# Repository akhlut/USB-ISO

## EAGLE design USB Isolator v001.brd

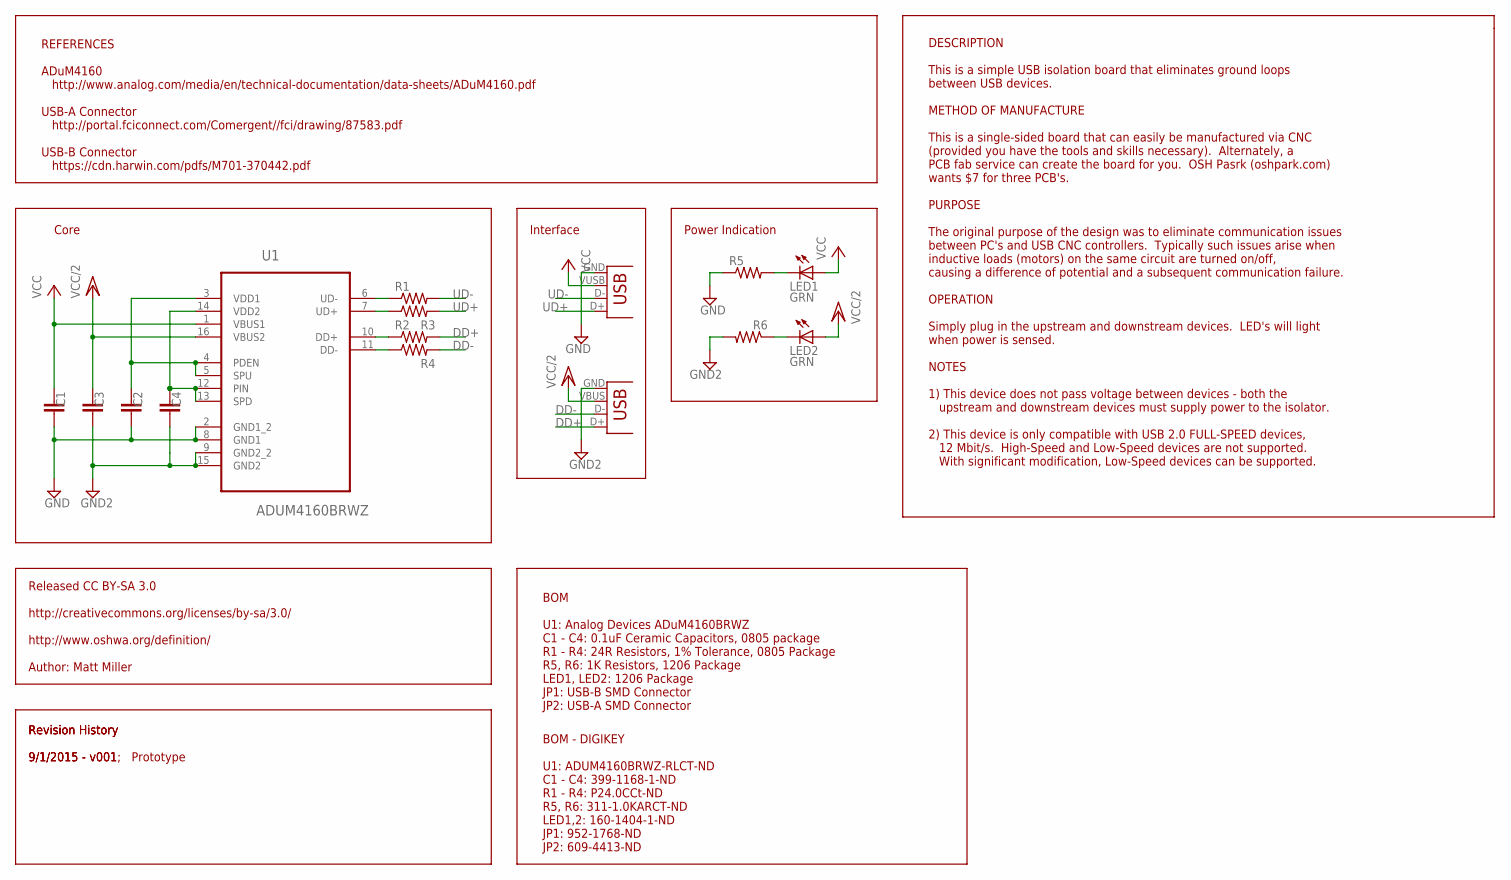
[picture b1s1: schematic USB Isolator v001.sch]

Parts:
C1, C2, C3, C4: 0.1uF; 0805
JP1: USB-B-S; USB-B-SMT
JP2: USB-A-S
LED1, LED2: GRN; LED-1206
R1, R2, R3, R4: 25; 0805
R5, R6: 1K; 1206
U1: ADUM4160BRWZ; SOIC127P1032X265-16N

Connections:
DD+: JP2.D+, R4.2
DD-: JP2.D-, R3.2
GND: C1.2, C2.2, JP1.GND, R5.1, U1.2 (GND1_2), U1.8 (GND1)
GND2: C3.2, C4.2, JP2.GND, R6.2, U1.9 (GND2_2), U1.15 (GND2)
unnamed: LED1.C, R5.2
unnamed: C2.1, U1.3 (VDD1), U1.4 (PDEN), U1.5 (SPU)
unnamed: LED2.C, R6.1
unnamed: C4.1, U1.12 (PIN), U1.13 (SPD), U1.14 (VDD2)
unnamed: R1.1, U1.6 (UD-)
unnamed: R2.1, U1.7 (UD+)
unnamed: R4.1, U1.10 (DD+)
unnamed: R3.1, U1.11 (DD-)
UD+: JP1.D+, R2.2
UD-: JP1.D-, R1.2
VCC: C1.1, JP1.VUSB (VBUS), LED1.A, U1.1 (VBUS1)
VCC/2: C3.1, JP2.VBUS, LED2.A, U1.16 (VBUS2)

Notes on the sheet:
REFERENCES ADuM4160 http://www.analog.com/media/en/technical-documentation/data-sheets/ADuM4160.pdf USB-A Connector http://portal.fciconnect.com/Comergent//fci/drawing/87583.pdf USB-B Connector https://cdn.harwin.com/pdfs/M701-370442.pdf
BOM U1: Analog Devices ADuM4160BRWZ C1 - C4: 0.1uF Ceramic Capacitors, 0805 package R1 - R4: 24R Resistors, 1% Tolerance, 0805 Package R5, R6: 1K Resistors, 1206 Package LED1, LED2: 1206 Package JP1: USB-B SMD Connector JP2: USB-A SMD Connector
Core
Interface
Power Indication
Released CC BY-SA 3.0 http://creativecommons.org/licenses/by-sa/3.0/ http://www.oshwa.org/definition/ Author: Matt Miller
DESCRIPTION This is a simple USB isolation board that eliminates ground loops between USB devices. METHOD OF MANUFACTURE This is a single-sided board that can easily be manufactured via CNC (provided you have the tools and skills necessary). Alternately, a PCB fab service can create the board for y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
Revision History 9/1/2015 - v001; Prototype
Revision History 9/1/2015 - v001
BOM - DIGIKEY U1: ADUM4160BRWZ-RLCT-ND C1 - C4: 399-1168-1-ND R1 - R4: P24.0CCt-ND R5, R6: 311-1.0KARCT-ND LED1,2: 160-1404-1-ND JP1: 952-1768-ND JP2: 609-4413-ND

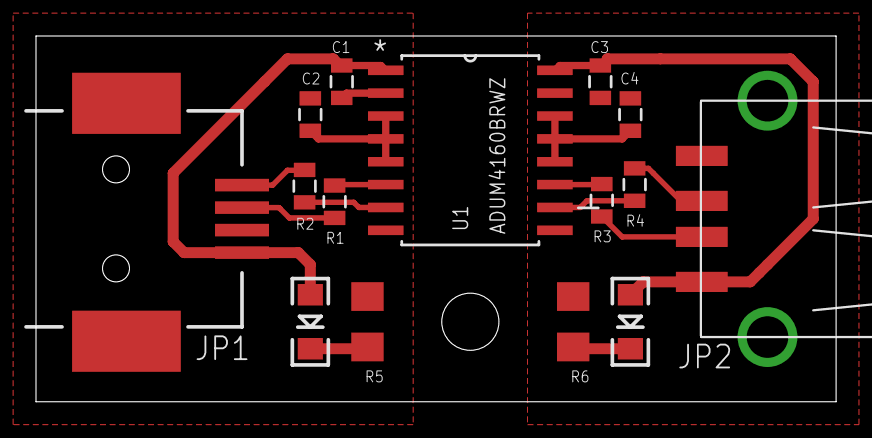
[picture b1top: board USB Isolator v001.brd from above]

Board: 2 copper layers, 44.5 x 20.3 mm, 16 parts (1 on the bottom side), 16 nets.

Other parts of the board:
U$1: OSHW-LOGO-L

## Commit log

2015-09-03 :boom::camel: Added .gitattributes
2015-09-03 USB Isolator

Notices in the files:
parts and their libraries:
SparkFun-Connectors: Licensing: CC v3.0 Share-Alike You are welcome to use this library for commercial purposes.
